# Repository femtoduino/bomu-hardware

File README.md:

# bomu-hardware
Bluetooth "TOMU" board

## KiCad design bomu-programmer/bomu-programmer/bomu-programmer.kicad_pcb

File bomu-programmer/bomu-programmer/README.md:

# BOMU Programmer

Using the SEGGER J-Link mini requires a recent install of openJDK, with the following in your bash or zsh profile script:

(MacOS)

```
export PATH="/usr/local/opt/openjdk/bin:$PATH"
export JAVA_HOME=/usr/local/opt/openjdk/
```

The command is `JLinkExe`, and you can connect to the device `NRF52840_XXAA` via SWD. Note: Requires external supply of 3V3!

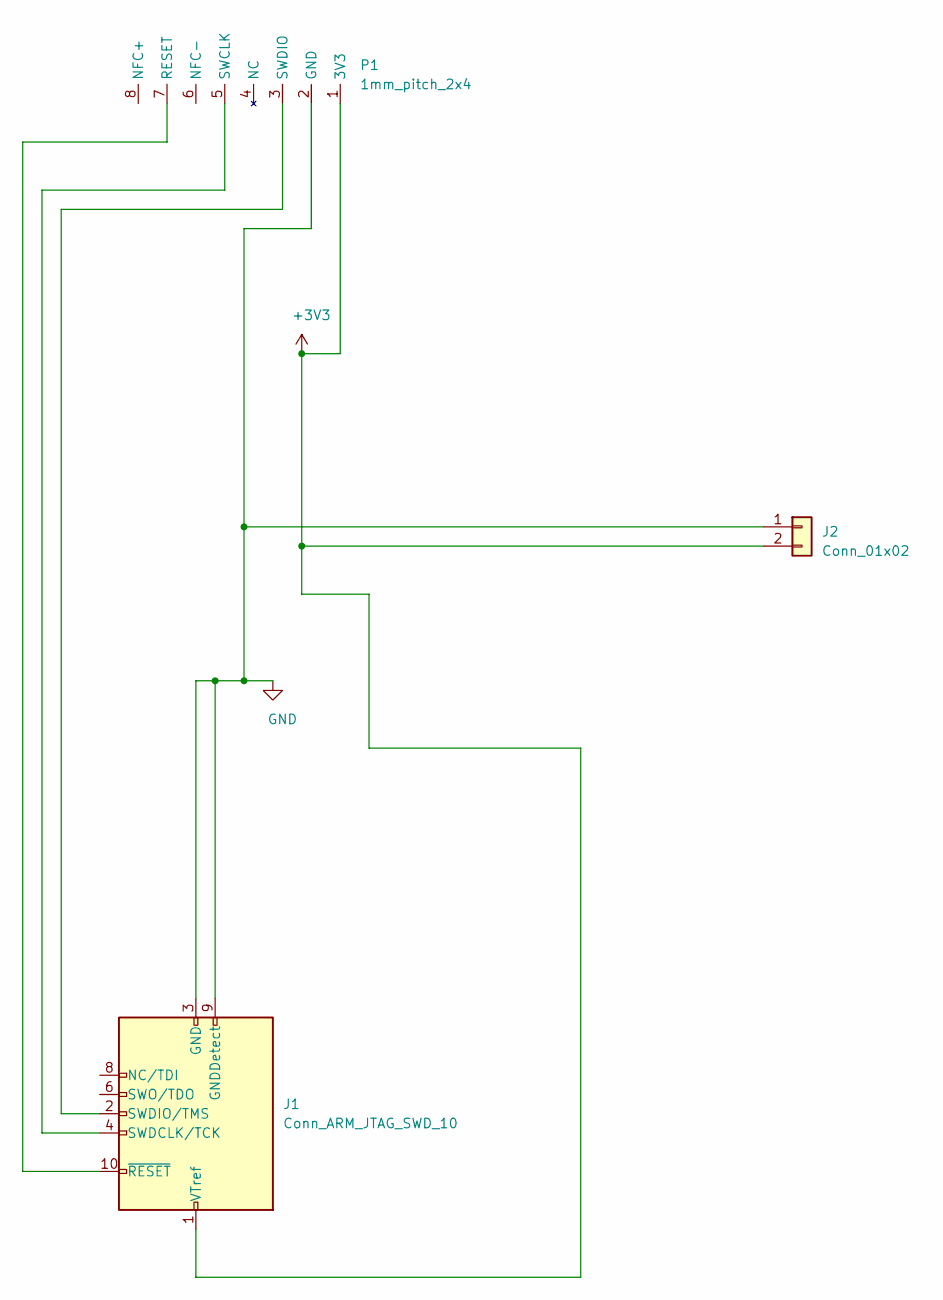
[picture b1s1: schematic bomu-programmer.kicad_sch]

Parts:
J1: Conn_ARM_JTAG_SWD_10; PinSocket_2x05_P1.27mm_Vertical_SMD
J2: Conn_01x02; PinHeader_1x02_P2.54mm_Vertical
P1: 1mm_pitch_2x4; pin_2x4_1mm

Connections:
+3V3: J1.1 (VTref), J2.2, P1.1 (3V3)
GND: J1.3 (GND), J1.5 (GND), J1.9 (GNDDetect), J2.1, P1.2 (GND)
unnamed: J1.4 (SWDCLK/TCK), P1.5 (SWCLK)
unnamed: J1.2 (SWDIO/TMS), P1.3 (SWDIO)
unnamed: J1.10 (~RESET), P1.7 (RESET)

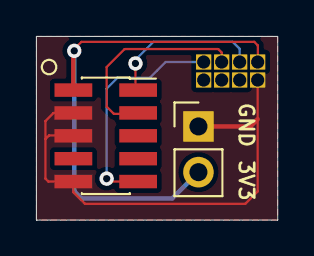
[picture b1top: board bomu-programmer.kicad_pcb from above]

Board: 2 copper layers, 13.4 x 10.2 mm, 3 parts (0 on the bottom side), 5 nets.

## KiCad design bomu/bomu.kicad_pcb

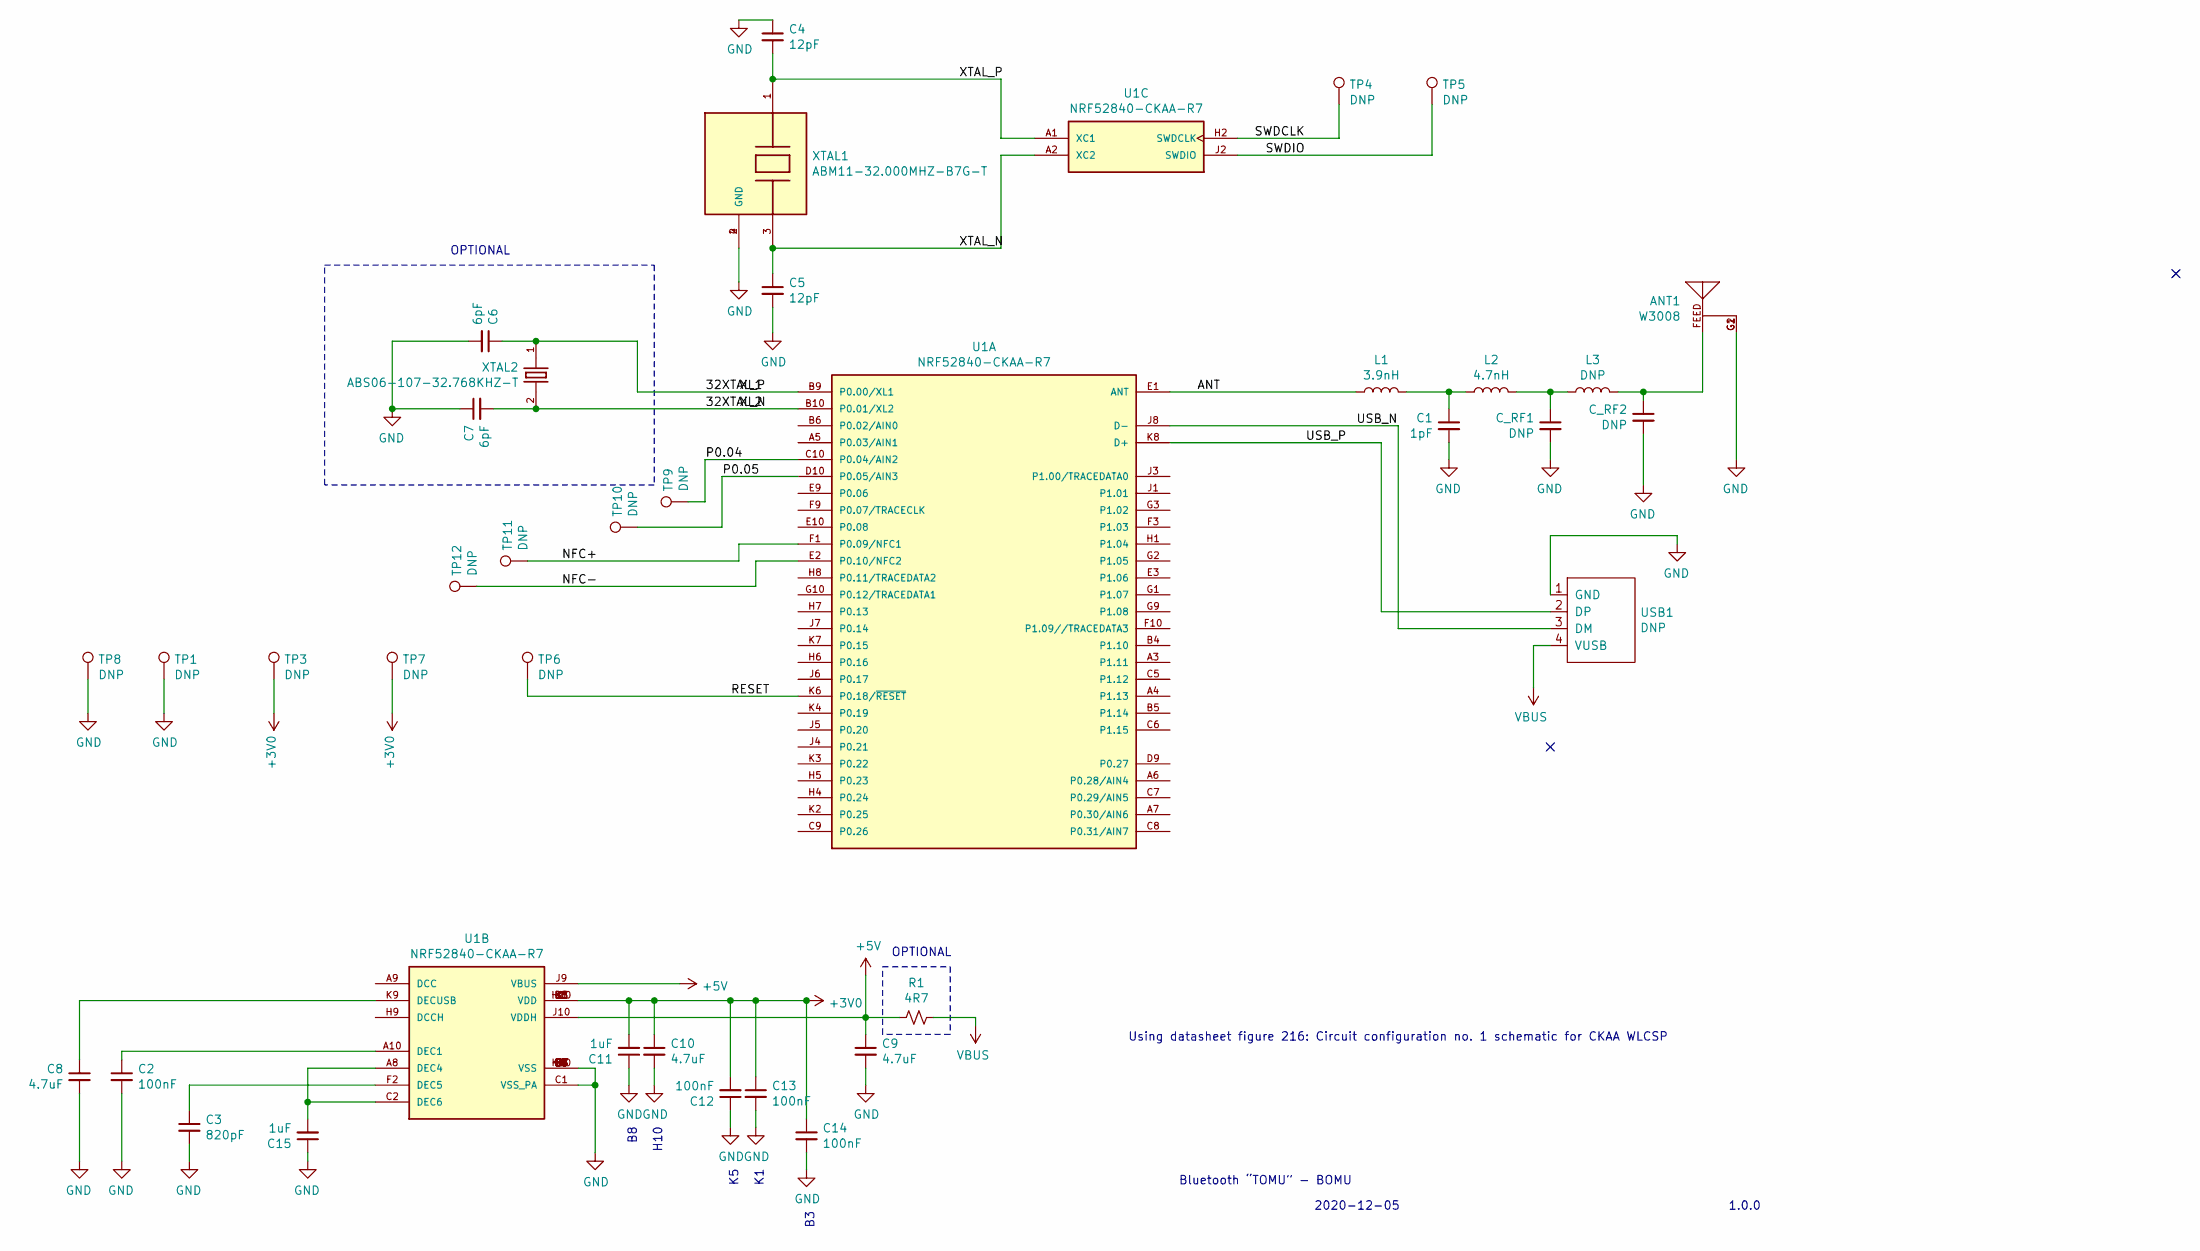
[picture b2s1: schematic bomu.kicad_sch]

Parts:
ANT1: W3008; ANTENNA_W3008
C1: 1pF; C_0201_0603Metric
C2, C12, C13, C14: 100nF; C_0201_0603Metric
C3: 820pF; C_0201_0603Metric
C4, C5: 12pF; C_0201_0603Metric
C6, C7: 6pF; C_0201_0603Metric
C8, C9, C10: 4.7uF; C_0402_1005Metric
C11, C15: 1uF; C_0402_1005Metric
C_RF1, C_RF2: DNP; C_0201_0603Metric
L1: 3.9nH; L_0201_0603Metric
L2: 4.7nH; L_0201_0603Metric
L3: DNP; L_0201_0603Metric
R1: 4R7; R_0201_0603Metric
TP1, TP3, TP4, TP5, TP6, TP7, TP8, TP9, TP10, TP11, TP12: DNP; TestPoint_Pad_D1.0mm
U1: NRF52840-CKAA-R7; BGA94N35P10X10_360X354X51N; PARTREV 1.1
USB1: DNP; USB_A_SOCKET_PCB_INSERT
XTAL1: ABM11-32.000MHZ-B7G-T; OSCCC200X160X59; DIGI-KEY_PART_NUMBER 535-10942-1-ND
XTAL2: ABS06-107-32.768KHZ-T; XTAL_ABS06-107-32.768KHZ-T

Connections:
+3V0: C10.1, C11.2, C12.2, C13.1, C14.1, TP3.1, TP7.1, U1.B3 (VDD), U1.B8 (VDD), U1.H10 (VDD), U1.K1 (VDD), U1.K5 (VDD)
+5V: C9.1, R1.2, U1.J9 (VBUS), U1.J10 (VDDH)
/32XTAL_N: C7.2, U1.B10 (P0.01/XL2), XTAL2.2
/32XTAL_P: C6.1, U1.B9 (P0.00/XL1), XTAL2.1
/ANT: L1.2, U1.E1 (ANT)
/NFC+: TP11.1, U1.F1 (P0.09/NFC1)
/NFC-: TP12.1, U1.E2 (P0.10/NFC2)
/P0.04: TP9.1, U1.C10 (P0.04/AIN2)
/P0.05: TP10.1, U1.D10 (P0.05/AIN3)
/RESET: TP6.1, U1.K6 (P0.18/~RESET)
/SWDCLK: TP4.1, U1.H2 (SWDCLK)
/SWDIO: TP5.1, U1.J2 (SWDIO)
/USB_N: U1.J8 (D-), USB1.3 (DM)
/USB_P: U1.K8 (D+), USB1.2 (DP)
/XTAL_N: C5.1, U1.A2 (XC2), XTAL1.3
/XTAL_P: C4.2, U1.A1 (XC1), XTAL1.1
GND: ANT1.G1, ANT1.G2, C1.2, C2.2, C3.2, C4.1, C5.2, C6.2, C7.1, C8.2, C9.2, C10.2, C11.1, C12.1, C13.2, C14.2, C15.1, C_RF1.2, C_RF2.2, TP1.1, TP8.1, U1.B7 (VSS), U1.C1 (VSS_PA), U1.C4 (VSS), U1.D3 (VSS), U1.D4 (VSS), U1.D5 (VSS), U1.D6 (VSS), U1.D7 (VSS), U1.D8 (VSS), U1.E4 (VSS), U1.E5 (VSS), U1.E6 (VSS), U1.E7 (VSS), U1.E8 (VSS), U1.F4 (VSS), U1.F5 (VSS), U1.F6 (VSS), U1.F7 (VSS), U1.F8 (VSS), U1.G4 (VSS), U1.G5 (VSS), U1.G6 (VSS), U1.G7 (VSS), U1.G8 (VSS), U1.K10 (VSS), USB1.1 (GND), XTAL1.2 (GND), XTAL1.4 (GND)
unnamed: ANT1.FEED, C_RF2.1, L3.1
unnamed: C1.1, L1.1, L2.2
unnamed: C_RF1.1, L2.1, L3.2
unnamed: C2.1, U1.A10 (DEC1)
unnamed: C15.2, U1.A8 (DEC4), U1.C2 (DEC6)
unnamed: C3.1, U1.F2 (DEC5)
unnamed: C8.1, U1.K9 (DECUSB)
VBUS: R1.1, USB1.4 (VUSB)

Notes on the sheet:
H10
OPTIONAL
1.0.0
2020-12-05
Bluetooth “TOMU” - BOMU
Using datasheet figure 216: Circuit configuration no. 1 schematic for CKAA WLCSP

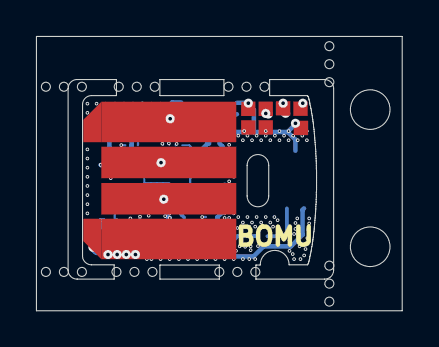
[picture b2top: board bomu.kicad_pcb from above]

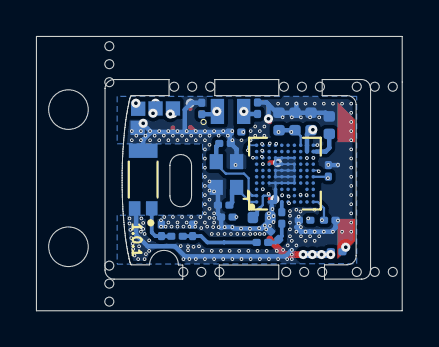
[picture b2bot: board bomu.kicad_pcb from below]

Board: 6 copper layers, 20.3 x 15.2 mm, 37 parts (29 on the bottom side), 25 nets.

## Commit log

2020-12-05 LFS track PDF files
2020-12-06 Initial work on BOMU schematic. Will need to swap out QFN for WLCSP design instead
2020-12-06 Adding WLCSP footprint and symbol
2020-12-06 Swapped QFN for WLCSP
2020-12-06 Cleaning up schematic
2020-12-06 Added remaining components to schematic
2020-12-06 Adding USB symbol. Will need custom USB A tab footprint
2020-12-06 Adding nRF52840 datasheet document (PDF)
2020-12-06 Updating schematic info
2020-12-06 Adding custom USB A tab insert symbol and footprint. Started work on PCB
2020-12-15 Current work on the PCB
2020-12-15 Changing from 2-lyaer to 4-layer
2020-12-15 Updating footprints. Adding SWD pads
2020-12-15 Adjusting pour around antenna footprint. Adding more traces
2020-12-23 Current work on ground planes
2020-12-23 Adding ground plane stitching with microvias
2020-12-25 Current progress on BOMU 1.0.0
2020-12-27 Adding gerbers, and current work
2020-12-27 PCB design edits
2021-01-03 Latest changes to the schematic and pcb
2021-01-06 Tonight's work on bomu. Added LC filter to VDD3P3 pins
2021-01-18 Latest work on BOMU design
2021-01-18 Adjusting 3D model paths for component 3D models. Adding gerbers
2021-01-21 Updating schematic KiCAD version. Updating antenna tuning component footprint placements
2021-01-21 Updating gerbers, drills, etc
2021-02-12 Added CPWG ground layer cutouts under RF component footprints
2021-12-15 Current work on BOMU 1.0.1, which address two known design defects in 1.0.0
2021-12-18 Current work on BOMU 1.0.1 and gerber/drill outputs
2021-12-18 Adding BoM partslist to repository
2021-12-23 DRC violation corrections, regenerated gerbers, re-rendered 3D render as a JPEG
2021-12-23 Setting view to high contrast mode
2021-12-23 Upgrading file format to KiCAD 6.0
2021-12-31 Updating to use the stable KiCAD 6.0 release, adjusting mouse_bites footprint
2022-02-18 Addressing two (2) defects found in 1.0.0, reducing the amount of excess ground layer stitching, and addressing swapped USB data pins (corrected in 1.0.1)
2022-02-19 Adjusting a ground trace from the antenna, regenerated gerber files, adding layer stackup txt file
2023-03-18 Upgrading for KiCAD 7.x format. Adding PDF of bomu-programmer PCB
2023-04-04 Updating for KiCAD 7. Updated bomu-programmer board. Gerbers for bomu-programmer generated.
